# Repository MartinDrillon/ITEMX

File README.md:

# ITEMX
Ortholinear split keyboard using ZMK and Xiao Seeed BLE"

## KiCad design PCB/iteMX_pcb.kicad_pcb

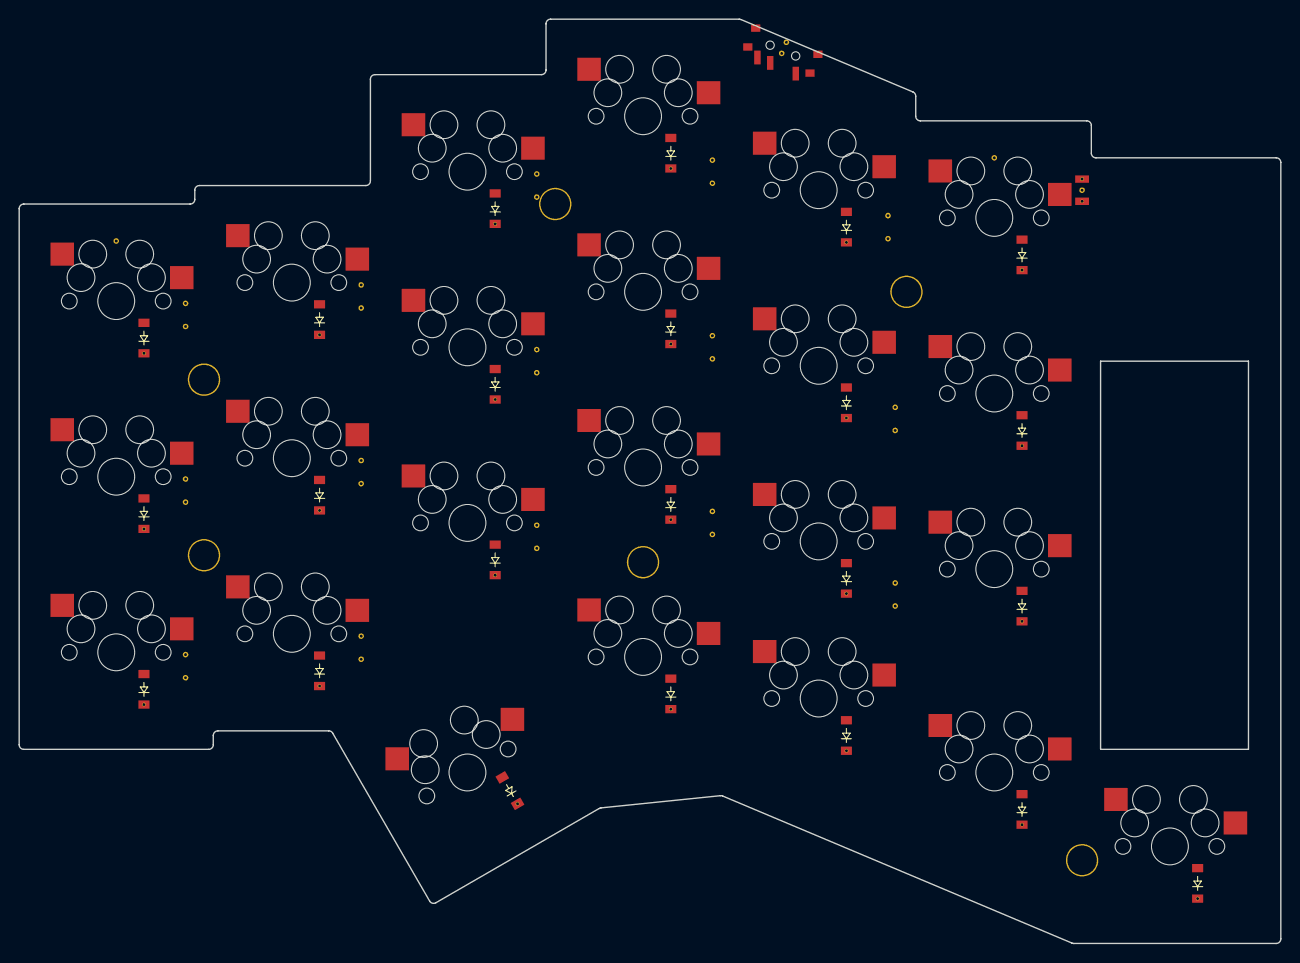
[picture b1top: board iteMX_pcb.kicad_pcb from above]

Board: 2 copper layers, 136.5 x 100.0 mm, 47 parts (0 on the bottom side), 34 nets, no tracks yet.

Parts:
D1, D2, D3, D4, D5, D6, D7, D8, D9, D10, D11, D12, D13, D14, D15, D16, D17, D18, D19, D20, D21, D22, D23: diode_via
D25: connecteur_batterie
S1, S2, S3, S4, S5, S6, S7, S8, S9, S10, S11, S12, S13, S14, S15, S16, S17, S18, S19, S20, S21, S22, S23: mx_hotswapp

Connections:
GND: D25.1, D25.2
alt_first: D19.2, S19.1
col_1: S1.2, S2.2, S3.2
col_2: S4.2, S5.2, S6.2, S19.2
col_3: S7.2, S8.2, S9.2, S20.2
col_4: S10.2, S11.2, S12.2, S21.2
col_5: S13.2, S14.2, S15.2, S22.2
col_6: S16.2, S17.2, S18.2, S23.2
ctrl_first: D20.2, S20.1
e_first: D22.2, S22.1
index_bottom: D13.2, S13.1
index_home: D14.2, S14.1
index_top: D15.2, S15.1
inner_bottom: D16.2, S16.1
inner_home: D17.2, S17.1
inner_top: D18.2, S18.1
layer_first: D23.2, S23.1
middle_bottom: D10.2, S10.1
middle_home: D11.2, S11.1
middle_top: D12.2, S12.1
outer_bottom: D1.2, S1.1
outer_home: D2.2, S2.1
outer_top: D3.2, S3.1
pinkie_bottom: D4.2, S4.1
pinkie_home: D5.2, S5.1
pinkie_top: D6.2, S6.1
pos: D25.1, D25.2
ring_bottom: D7.2, S7.1
ring_home: D8.2, S8.1
ring_top: D9.2, S9.1
row_1: D3.1, D6.1, D9.1, D12.1, D15.1, D18.1
row_2: D2.1, D5.1, D8.1, D11.1, D14.1, D17.1
row_3: D1.1, D4.1, D7.1, D10.1, D13.1, D16.1
row_4: D19.1, D20.1, D21.1, D22.1, D23.1
shift_first: D21.2, S21.1

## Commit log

2024-02-01 création des dossiers
2024-02-01 ajout pcb
2024-02-01 ajout gerber, ergogen et case
2024-02-01 ajout zmk_config
2024-02-01 suppression zmk_config
2024-02-01 deuxième essai zmk_config
2024-02-01 essai action zmk_config
2024-02-01 ajout readme
2024-02-01 modification readme
2024-02-03 ajout config itemx readme
2024-02-03 nettoyage keymap
2024-02-05 Rename BASE.png to base.png
2024-02-05 Rename CUMBO.png to cumbo.png
